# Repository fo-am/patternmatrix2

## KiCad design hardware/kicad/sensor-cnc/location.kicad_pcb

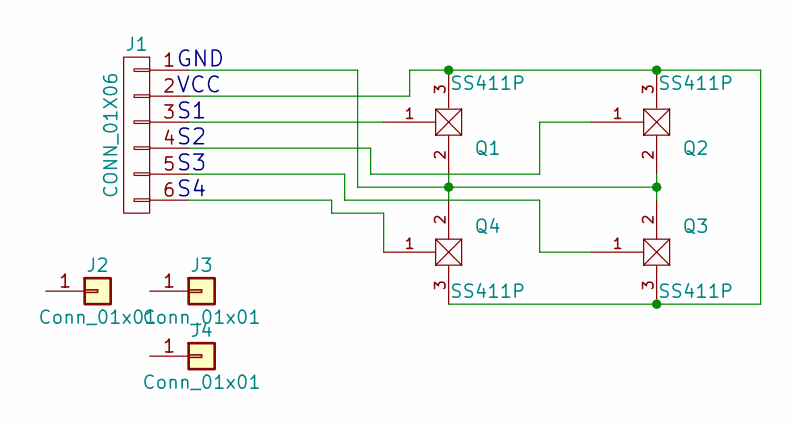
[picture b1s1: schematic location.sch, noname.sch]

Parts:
J1: CONN_01X06; Pin_Header_Straight_1x06_Pitch2.54mm
J2, J3, J4: Conn_01x01; 1pin
Q1, Q2, Q3, Q4: SS411P; TO-92_Horizontal1_Inline_Narrow_Oval

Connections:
unnamed: J1.1, Q1.2 (B), Q2.2 (B), Q3.2 (B), Q4.2 (B)
unnamed: J1.2, Q1.3 (E), Q2.3 (E), Q3.3 (E), Q4.3 (E)
unnamed: J1.3, Q1.1 (C)
unnamed: J1.4, Q2.1 (C)
unnamed: J1.5, Q3.1 (C)
unnamed: J1.6, Q4.1 (C)

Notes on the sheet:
GND
VCC

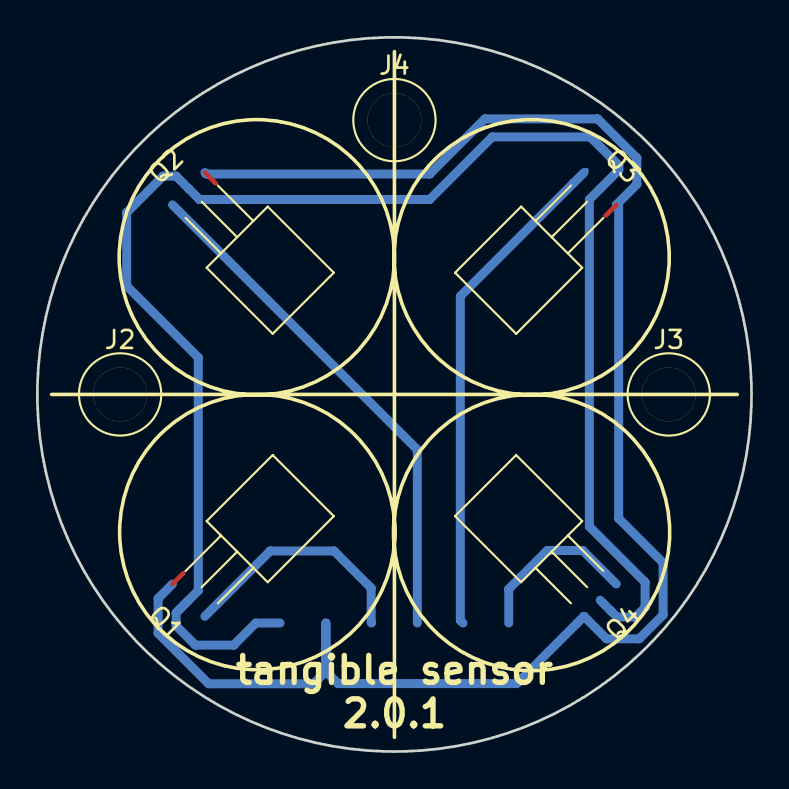
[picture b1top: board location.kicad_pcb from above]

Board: 2 copper layers, 39.7 x 39.7 mm, 8 parts (1 on the bottom side), 6 nets.

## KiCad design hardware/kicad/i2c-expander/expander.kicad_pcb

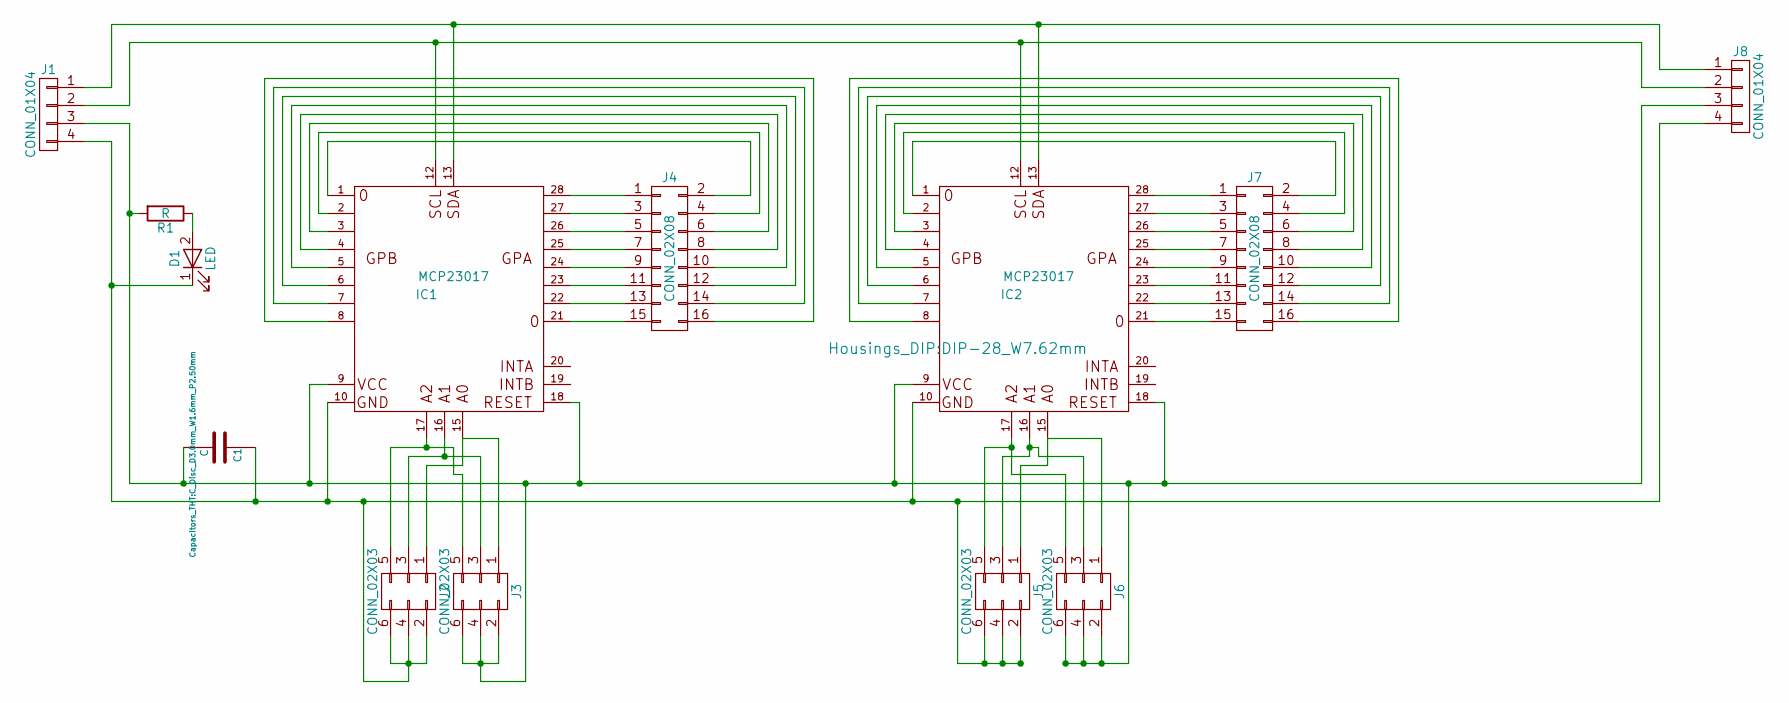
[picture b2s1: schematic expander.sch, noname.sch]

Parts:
C1: C; C_Disc_D3.0mm_W1.6mm_P2.50mm
D1: LED; LED_D3.0mm
IC1, IC2: MCP23017; DIP-28_W7.62mm
J1, J8: CONN_01X04; Pin_Header_Straight_1x04_Pitch2.54mm
J2, J3, J5, J6: CONN_02X03; Pin_Header_Straight_2x03_Pitch2.54mm
J4, J7: CONN_02X08; Pin_Header_Straight_2x08_Pitch2.54mm
R1: R; R_Axial_DIN0204_L3.6mm_D1.6mm_P5.08mm_Horizontal

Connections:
unnamed: C1.1, D1.1 (K), IC1.10, IC2.10, J1.4, J2.2, J2.4, J2.6, J5.2, J5.4, J5.6, J8.4
unnamed: C1.2, IC1.9, IC1.18, IC2.9, IC2.18, J1.3, J3.2, J3.4, J3.6, J6.2, J6.4, J6.6, J8.3, R1.2
unnamed: D1.2 (A), R1.1
unnamed: IC1.1 (C), J4.2
unnamed: IC1.2 (B), J4.4
unnamed: IC1.3 (E), J4.6
unnamed: IC1.4 (GBP_3), J4.8
unnamed: IC1.5, J4.10
unnamed: IC1.6, J4.12
unnamed: IC1.7, J4.14
unnamed: IC1.8, J4.16
unnamed: IC1.12, IC2.12, J1.2, J8.2
unnamed: IC1.13, IC2.13, J1.1, J8.1
unnamed: IC1.15, J2.1, J3.1
unnamed: IC1.16, J2.3, J3.3
unnamed: IC1.17, J2.5, J3.5
unnamed: IC1.21, J4.15
unnamed: IC1.22, J4.13
unnamed: IC1.23, J4.11
unnamed: IC1.24, J4.9
unnamed: IC1.25, J4.7
unnamed: IC1.26, J4.5
unnamed: IC1.27, J4.3
unnamed: IC1.28, J4.1
unnamed: IC2.1 (C), J7.2
unnamed: IC2.2 (B), J7.4
unnamed: IC2.3 (E), J7.6
unnamed: IC2.4 (GBP_3), J7.8
unnamed: IC2.5, J7.10
unnamed: IC2.6, J7.12
unnamed: IC2.7, J7.14
unnamed: IC2.8, J7.16
unnamed: IC2.15, J5.1, J6.1
unnamed: IC2.16, J5.3, J6.3
unnamed: IC2.17, J5.5, J6.5
unnamed: IC2.21, J7.15
unnamed: IC2.22, J7.13
unnamed: IC2.23, J7.11
unnamed: IC2.24, J7.9
unnamed: IC2.25, J7.7
unnamed: IC2.26, J7.5
unnamed: IC2.27, J7.3
unnamed: IC2.28, J7.1

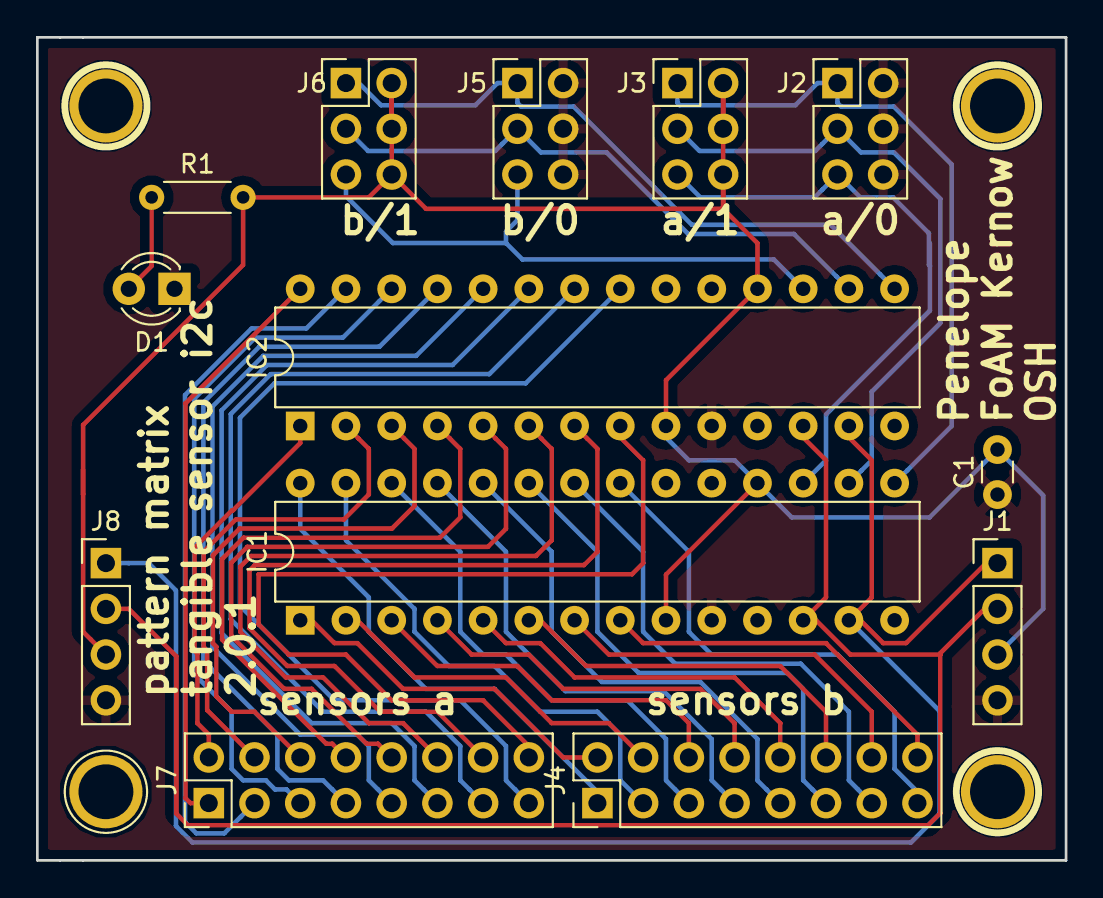
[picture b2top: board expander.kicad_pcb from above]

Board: 2 copper layers, 57.1 x 45.7 mm, 13 parts (0 on the bottom side), 43 nets.

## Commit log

2017-06-06 sent for production
2017-06-28 added svg plots
2017-06-30 added wood protectors
2017-07-10 Laser/CNC shapes for circuit covers and tokens
    Contains separate layers for circuit board covers (top and base) and various shapes of token.
2017-07-14 added driver
2017-08-03 filtering added to driver
2017-08-04 row test
2017-08-10 starting to arrange sensors properly
2017-08-10 connected to sound
2017-08-11 sounds
2017-08-11 flipped mcp 7
2017-08-11 perf tweaks
2017-08-21 added os stuff, just in case
2017-08-21 tokens properly read
2017-08-21 debug sev seg led
2017-08-23 bar locking
2017-08-25 added scale block
2017-08-25 missing files
2017-08-29 startup rejig, fixed with delay
2017-08-29 added warpweighted sim
2017-08-31 weaving sim fixes
2017-08-31 added bpm mult
2017-09-01 removed sync and switch voice reset
2017-09-03 some new sounds and eq
2017-09-04 removed loud noise bar sync bpm mult fix
2017-09-05 reduced volume and pitch of pads
2017-09-27 added AR stuff
2017-10-12 sending to AR and jack audio startup
2017-10-12 seq feedback
2017-10-18 added pointy extruded things
2017-10-19 new setup for algomech
2017-10-19 ungrowing things
2017-10-31 ar over wifi
2017-10-31 weaving sim fixes for algomech
2017-11-03 algomech changes and new 4x4 pattern matrix driver
2018-01-10 added tabletloom
2018-01-10 vertcols changes
2018-01-10 tangible tablet weaving
2018-01-12 updated startup script
2018-01-27 manual, and new pcb
2018-01-27 manual edits
2018-06-08 added robotics programming stuff
2018-06-15 8x8 warpweighted loom
2018-06-22 robotics stuff from munich workshop
2018-10-03 pre-munich trip update
2018-10-03 added python osc
2018-10-04 changes for the big matrix version
2018-10-04 update from munich version with fabric pattern matrix setup
2018-10-04 added osc server
2018-10-04 added gitignore
2019-03-04 added thread sensor version with i2c
2020-01-17 fixed i2c addresses in sensor firmware
2022-02-22 added webserial firmware
